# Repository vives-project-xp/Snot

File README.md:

# SNOT

Safe Night Out Together is een project waar er wordt geprobeerd om spiking zo veel mogelijk tegen te houden. Wij hebben een dop ontwikkeld die dir probeerd tegen te houden. De bedoeling is dat je een nfc bandje scant op de dop en dat deze dan open zal gaan, als deze eraf wordt geforceerd zal er een lichtje branden, die de persoon inlicht om het drankje weg te gieten.

## Discord

Join het discord kanaal voor alle info en vragen: [Discord](https://discord.gg/33ayYHaHzA))

Bekijk ook onze [promovideo!](https://www.youtube.com/watch?v=ft7jXlZkHr0&feature=youtu.be)

Zie ook:  [Redmine](https://project.devbit.be/projects/snot)

## Dop Design

Voorlopig hebben we een aantal designs gehad. Het laatste design is de blauwe dop.
Zie discord INFO/Design voor verdere info.

Dit is een foto van de dop, in het grote gat komt een servo motor, die het glas klem zet. Er zit ook nog een dubbele bodem in voor de pcb, maar die hebben we niet kunnen uittesten.

Dit is een foto van het deurtje dat de servo motor zal in plaats houden en beschermen.

## PCB Design

Om de shield te laten werken moet je hem in SPI mode zetten. Voor SPI moet je SEL0 en SEL1 sluiten, je moet ze dus dichtsolderen of met een schakelaar connecteren.

Om de shield te verbinden met bv. een nucleo moet je 3 power pinnen(5V, 3V3 en GND) en 4 spi pinnen(MOSI, MISO, SCK, en CS/SS) verbinden.

In het mapje bcp staat er een mapje snot_pcb. Hierin staat de kicad file voor de pcb, deze kan gebruikt worden om de pcb online te bestellen. Er staat ook een BOM lijst met de benodigde materialen. 

## Benodigdheden Software

- Installeren van Visual Studio Code: <https://code.visualstudio.com/> // + Benodigde extenties (zou moeten automatisch aanbieden welke je nodig hebt)
- Installeren van python: <https://www.academicsoftware.eu/software/27/265> // Take the lastest STABLE release
- Installeren van (mini)conda: <https://software-installation-guide.netlify.app/conda/>
- Installeren van mbed: <https://software-installation-guide.netlify.app/mbed/>
- Installeren van KiCad: <https://www.kicad.org/download/windows/> // CERN Switzerland
- Installeren van SolidEdge: <https://www.academicsoftware.eu/software/25/292>

Zorg er ook voor dat miniconda is toegevoegd aan je omgevings variabelen: bv. C:\Users\thybr\miniconda3\Scripts

## Code

Voor het binnenhalen van de code en overige:
```bash
git clone https://github.com/vives-project-xp/Snot.git
git checkout snot-v2
```

De volledige code is terug te vinden onder de file 'mbed'.
Indien je de schakeling wil testen zonder de NFC maar enkel met drukknoppen moet je de file 'cap' gebruiken

Voor het compileren van de code:

- Open powershell
- Conda create mbed (zie installation guide (mini)conda)
- Conda activate mbed (zie installation guide (mini)conda voor installatie extensies)
- Compileren van de code
```bash 
mbed compile -f
```

Er is ook code voor de box, maar die heeft zijn eigen README.md.
Deze code was van een vorig project en wij hebben die aangepast voor ons project. Er zijn teveel files die we niet gebruiken, maar alle klasses zijn met elkaar verbonden en hierdoor is het te veel werk om de bestanden te verwijderen die we niet gebruiken. In citygame-displaydriver/Display.cpp is most of the code.

## Opstelling Cap 

[Hier](https://www.instagram.com/reel/CrSmLBvvxVR/?utm_source=ig_web_copy_link) is een demo van de opstelling.

Dit is de schakeling die gebruikt wordt in de demo, deze heeft 2 knoppen. 1 knop hiervan simuleert de nfc, omdat wij deze nog niet hebben. Het filmpje legt ook uit hoe deze precies werkt.

## NFC

There is code for the NFC included, but we haven't been able to test it out. In the code for the box, there is a file called citygame-displaydriver/Display.cpp. This is where most of the code for the box is and here you will have to add your own NFC code.

## Benodigdheden Hardware

- Cap + valse bodem + dekseltje motor
- STM32L467RG voor compilatie
- PN532 (versie blauw) voor scannen van de NFC --> soort versie kan nog veranderen ondertussen
- Zelfgemaakte PCB wanneer werken voor STM te vervangen (zou moeten in cap passen)
- PN532 (versie rood) voor het scannen van de NFC (zou moeten in de cap passen)
- Alle bestelde hardware + deze solderen op de zelf gemaakte PCB (zie mapje pcb)

## TODO

- De pcb solderen en dan NFC daarin implementeren
- NFC code voor de box maken

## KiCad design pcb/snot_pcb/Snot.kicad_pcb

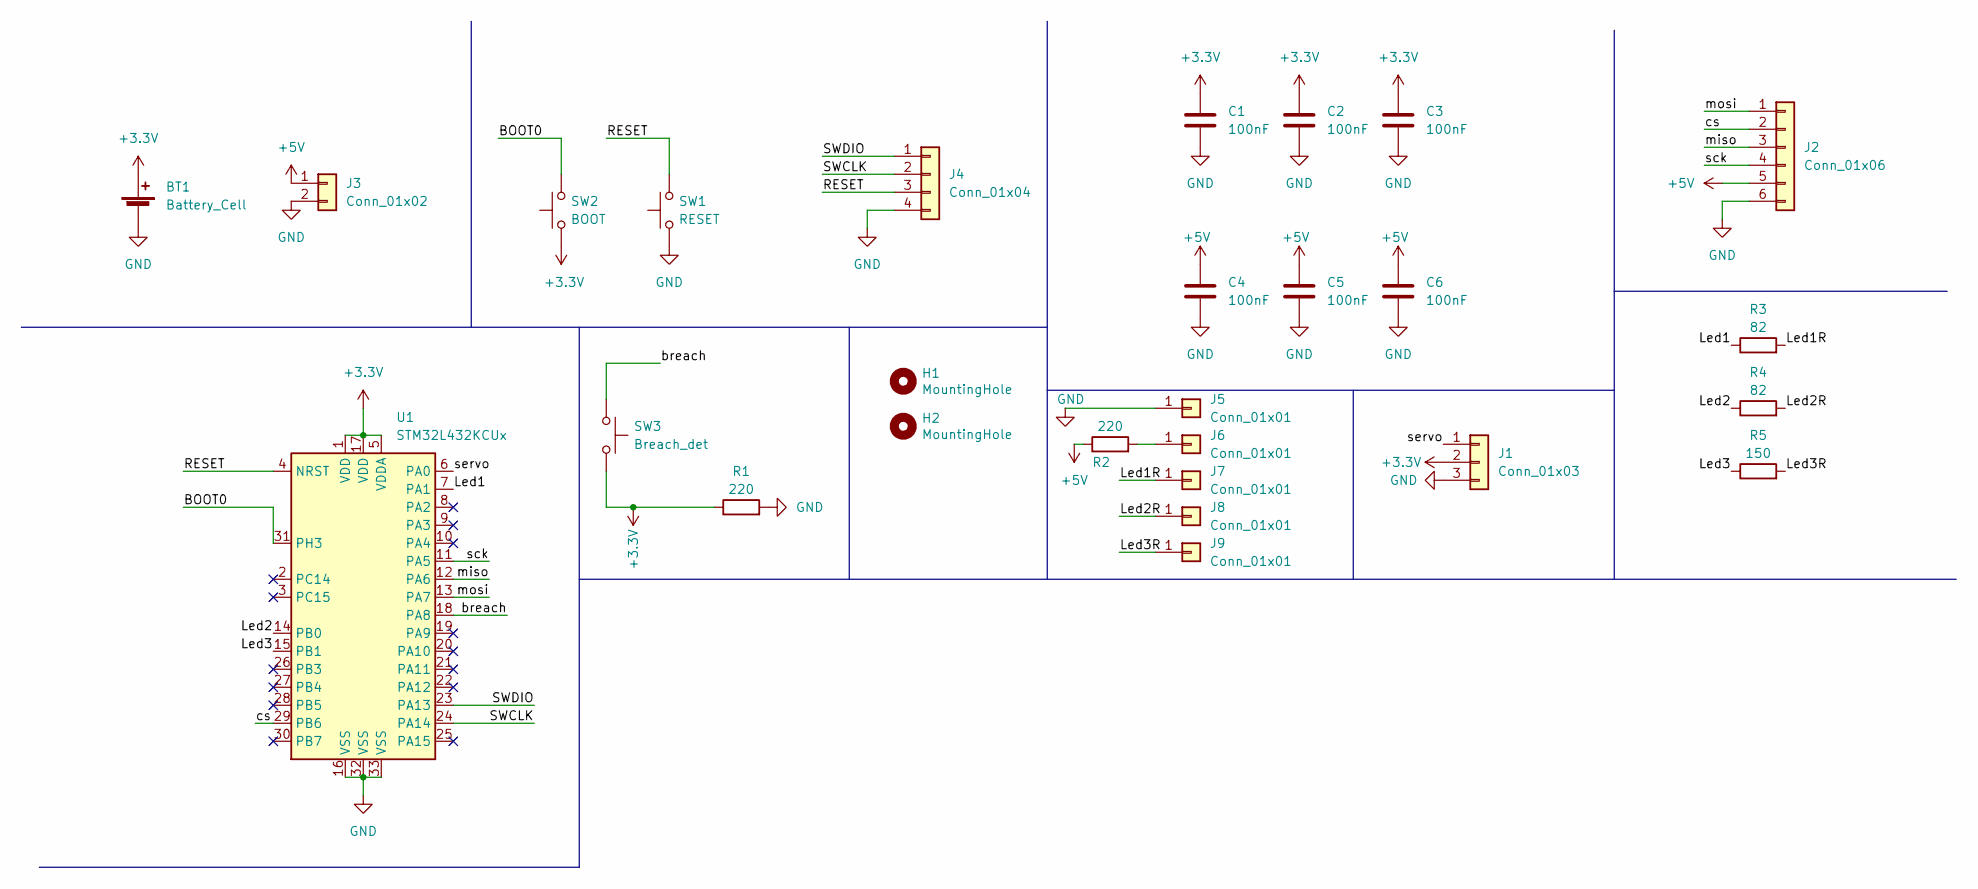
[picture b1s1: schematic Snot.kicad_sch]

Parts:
BT1: Battery_Cell; BatteryHolder_Keystone_3002_1x2032
C1, C2, C3, C4, C5, C6: 100nF; C_0603_1608Metric_Pad1.08x0.95mm_HandSolder
H1, H2: MountingHole; MountingHole_3.2mm_M3
J1: Conn_01x03; PinHeader_1x03_P2.54mm_Vertical
J2: Conn_01x06; PinHeader_1x06_P2.54mm_Vertical
J3: Conn_01x02; PinHeader_1x02_P2.54mm_Vertical
J4: Conn_01x04; PinHeader_1x04_P2.54mm_Vertical
J5, J6, J7, J8, J9: Conn_01x01; SolderWirePad_1x01_SMD_1x2mm
R1, R2: 220; R_0805_2012Metric_Pad1.20x1.40mm_HandSolder
R3, R4: 82; R_0805_2012Metric_Pad1.20x1.40mm_HandSolder
R5: 150; R_0805_2012Metric_Pad1.20x1.40mm_HandSolder
SW1: RESET; SolderJumper-2_P1.3mm_Open_Pad1.0x1.5mm
SW2: BOOT; SolderJumper-2_P1.3mm_Open_Pad1.0x1.5mm
SW3: Breach_det; SW_SPST_B3U-1000P
U1: STM32L432KCUx; QFN-32-1EP_5x5mm_P0.5mm_EP3.45x3.45mm

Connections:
+3V3: BT1.1 (+), C1.1, C2.1, C3.1, J1.2, R1.1, SW2.1, SW3.2, U1.1 (VDD), U1.5 (VDDA), U1.17 (VDD)
+5V: C4.1, C5.1, C6.1, J2.5, J3.1, R2.1
/BOOT0: SW2.2, U1.31 (PH3)
/Led1: R3.1, U1.7 (PA1)
/Led1R: J7.1, R3.2
/Led2: R4.1, U1.14 (PB0)
/Led2R: J8.1, R4.2
/Led3: R5.1, U1.15 (PB1)
/Led3R: J9.1, R5.2
/RESET: J4.3, SW1.2, U1.4 (NRST)
/SWCLK: J4.2, U1.24 (PA14)
/SWDIO: J4.1, U1.23 (PA13)
/breach: SW3.1, U1.18 (PA8)
/cs: J2.2, U1.29 (PB6)
/miso: J2.3, U1.12 (PA6)
/mosi: J2.1, U1.13 (PA7)
/sck: J2.4, U1.11 (PA5)
/servo: J1.1, U1.6 (PA0)
GND: BT1.2 (-), C1.2, C2.2, C3.2, C4.2, C5.2, C6.2, J1.3, J2.6, J3.2, J4.4, J5.1, R1.2, SW1.1, U1.16 (VSS), U1.32 (VSS), U1.33 (VSS)
unnamed: J6.1, R2.2

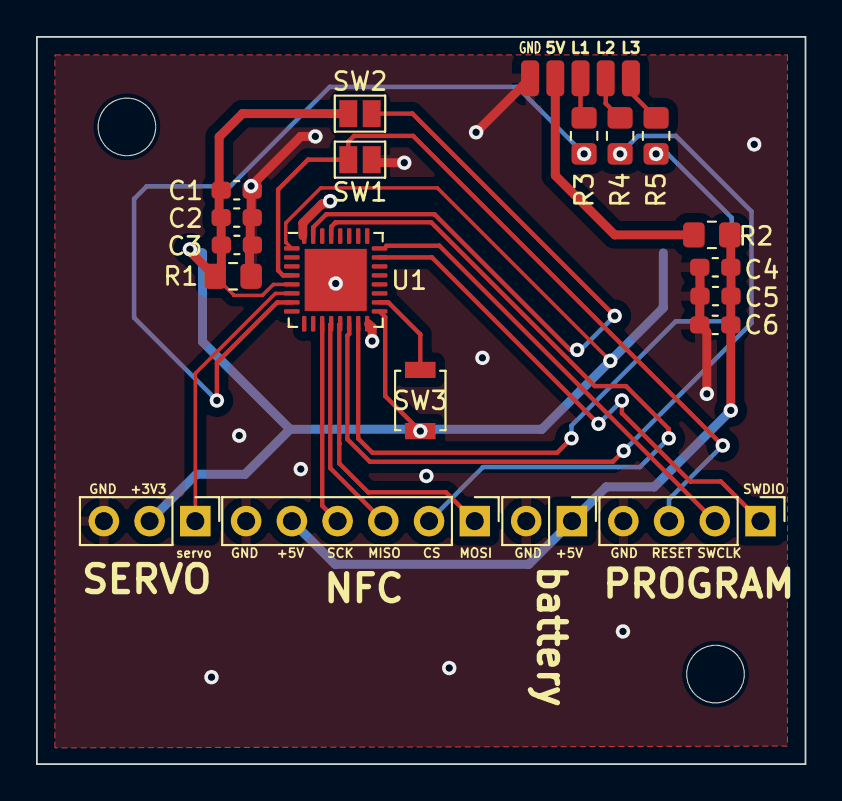
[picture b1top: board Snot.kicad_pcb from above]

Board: 2 copper layers, 42.7 x 40.4 mm, 27 parts (1 on the bottom side), 20 nets.

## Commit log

2022-10-06 Added current version of presentation
2022-10-06 Added folders
2022-10-13 Updated pptversion
2022-10-13 init
2022-10-18 add code for motor and servo
2022-10-20 mbed init and example NFC PARSER
2022-10-20 nfc branch init
2022-10-20 Added EEPROMDriver + Example code EEPROM Write/Read
2022-10-20 Revert "del"
    This reverts commit 30aab9238a53db8cd3b7c97d6f92209ddd0db00a.
2022-10-20 Added Makefile and Reader/Writer example for NFC
2022-10-20 Added comment for error logging
2022-10-20 Added files to ignore
2022-10-20 Added basic opening logic
2022-11-10 prototype code cap
2022-11-10 Debuged compiling error
2022-11-10 NFC example code not working, working on mbed-os/connec/nfc/src/NFCEEPROM.CPP
2022-11-24 working example
2022-11-24 organized filles
2022-11-24 not using m24 anymore
2022-11-24 removed old files and refactored main.cpp
2022-11-24 Updated README.md(Installation and working)
2022-11-24 added card saving and recognition
2022-11-24 old presentation
2022-11-24 add here your code
2022-11-24 Added master card
2022-11-24 fix master Card
2022-11-24 Updated Readme with mastertag info
2022-11-25 changed name
2022-11-25 deleting old files
2022-11-25 ignoring .vscode
2022-11-25 NFC main
2022-11-25 restoring servoExample
2022-11-28 makefile
2022-11-28 added comments
2022-11-28 implemented Servo - need to test
2022-12-01 readme.md
2022-12-01 Key generator for RFID
2022-12-01 adding password setter
2022-12-08 changed conda to miniconda to avoid confusion
2022-12-08 Added ledstrip Pinnames in comment
2022-12-08 added alternate pinnames
2022-12-08 Need to fix password
2022-12-08 finito
2022-12-08 PN532 documentation added
2022-12-08 Changed installation documentation
2022-12-08 remove multiple newlines
2022-12-08 Cleaned code from main and used helper object
2022-12-08 Added thread for blinking led
2022-12-15 Added Led class
2022-12-15 Implemented Led object
2022-12-15 fix RGB value used only rValue
2022-12-15 Adjusted pins for led
2022-12-15 Switched to single thread for blinks
2022-12-15 Switched RGB to green method
2022-12-15 merge
2022-12-15 Adjusted blinking
2022-12-15 Added master led signal
2022-12-15 fix typo in directory and fix whitespaces
2022-12-15 rgbled class with pinNames
2022-12-15 Solved merge
2022-12-15 Added info about code and mifare card
2022-12-15 typo
2022-12-15 Added blue light when pn532 board not found
2022-12-15 fix whitespaces
2022-12-15 Added flashing green light when saving new card
2022-12-15 Added light signals descritpions
2022-12-15 fix code format
2022-12-19 Added Comment
2022-12-19 test for button
2022-12-22 Added flag events for bad open
2022-12-22 Changed only master can reset LED open without NFC
2022-12-22 Added info about constant flashing red light
2023-03-14 1 button
2023-03-23 Initial commt
2023-03-23 citygame initial commit
2023-03-23 citygame broke
2023-03-29 cap works
2023-04-27 code box
2023-04-27 readme
2023-04-27 box README
2023-04-27 readme deels aangepast + extra bestanden
2023-04-27 small readme fix
2023-04-27 readme aangepast
2023-05-04 NFC in README.md
